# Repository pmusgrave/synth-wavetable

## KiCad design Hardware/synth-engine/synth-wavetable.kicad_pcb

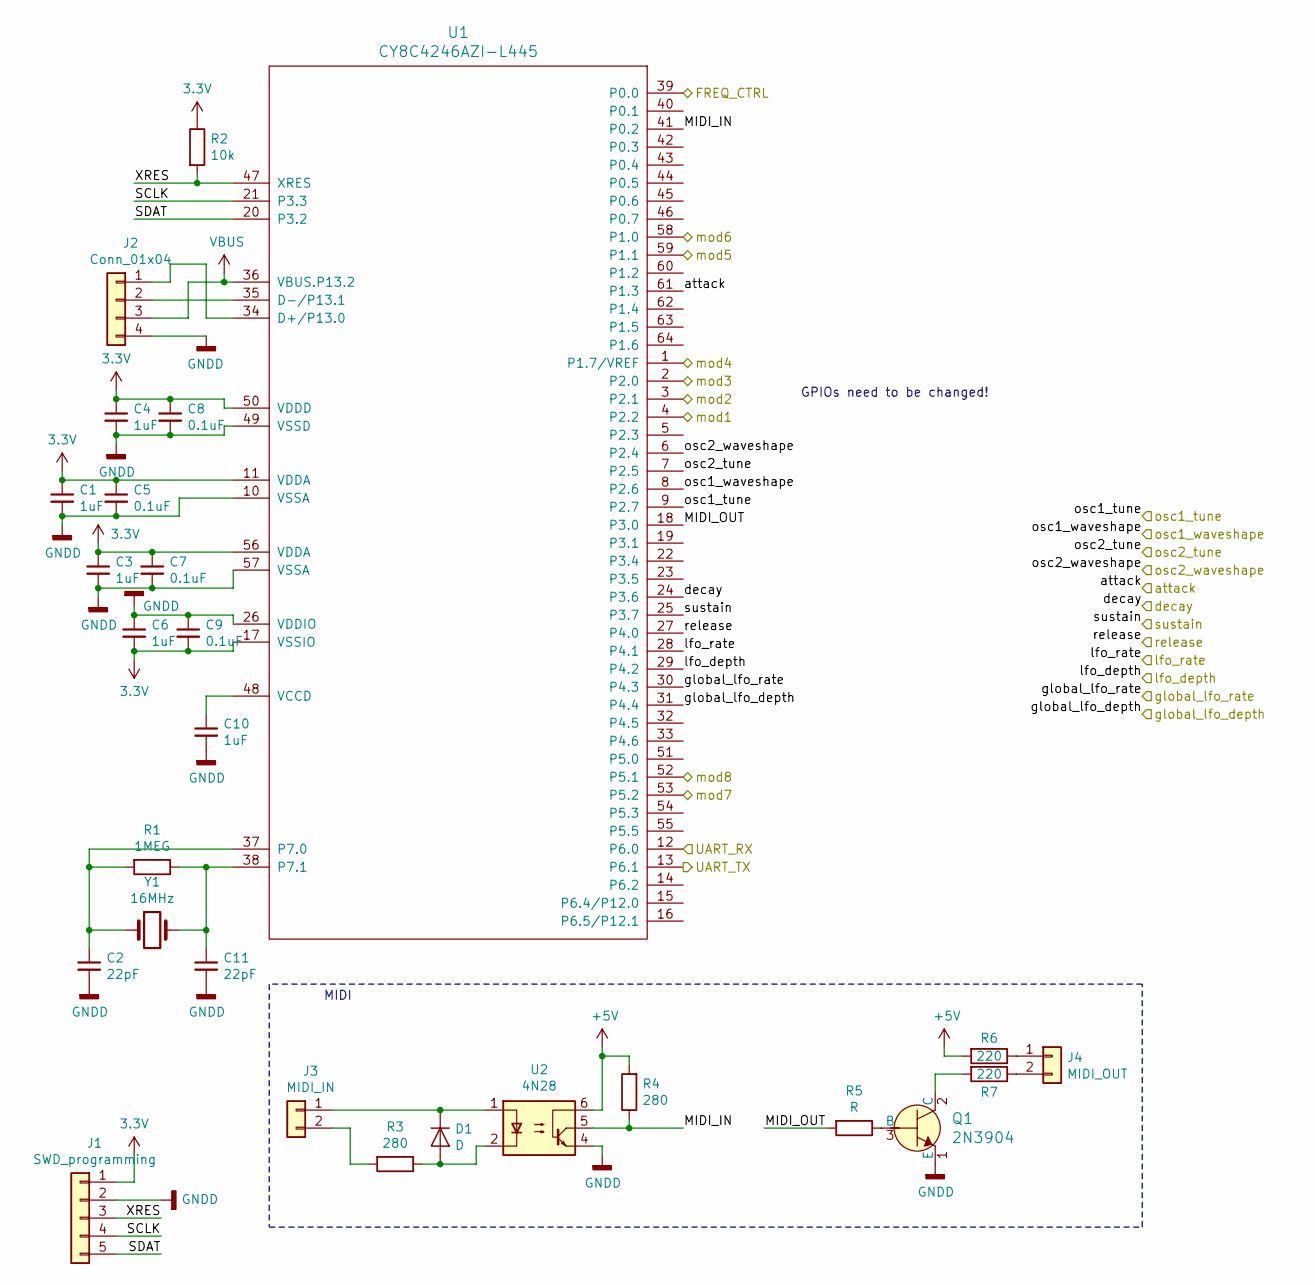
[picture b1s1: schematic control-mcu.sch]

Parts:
C1, C3, C4, C6, C10: 1uF; 0805
C2, C11: 22pF; 0805
C5, C7, C8, C9: 0.1uF; 0805
D1: D; 1210
J1: SWD_programming; 1X05
J2: Conn_01x04; 1X04
J3: MIDI_IN; 1X02
J4: MIDI_OUT; 1X02
Q1: 2N3904; SOT23-3; MPN 2N3904; Digi-Key_PN 2N3904CS-ND
R1: 1MEG; 0805
R2: 10k; 0805
R3, R4: 280; 0805
R5: R; 0805
R6, R7: 220; 0805
U1: CY8C4246AZI-L445; TQFP64
U2: 4N28; DIL-08
Y1: 16MHz; Crystal_SMD_HC49-SD_HandSoldering

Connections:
3.3V: C1.1, C3.1, C4.1, C5.1, C6.2, C7.1, C8.1, C9.2, J1.1, R2.1, U1.11 (VDDA), U1.17 (VSSIO), U1.50 (VDDD), U1.56 (VDDA); also elsewhere on the board
+5V: R4.2, R6.2, U2.6; also elsewhere on the board
/Connectors/attack: U1.61 (P1.3); also elsewhere on the board
/Connectors/decay: U1.24 (P3.6); also elsewhere on the board
/Connectors/global_lfo_depth: U1.31 (P4.4); also elsewhere on the board
/Connectors/global_lfo_rate: U1.30 (P4.3); also elsewhere on the board
/Connectors/lfo_depth: U1.29 (P4.2); also elsewhere on the board
/Connectors/lfo_rate: U1.28 (P4.1); also elsewhere on the board
/Connectors/mod1: U1.4 (P2.2); also elsewhere on the board
/Connectors/mod2: U1.3 (P2.1); also elsewhere on the board
/Connectors/mod3: U1.2 (P2.0); also elsewhere on the board
/Connectors/mod4: U1.1 (P1.7/VREF); also elsewhere on the board
/Connectors/mod5: U1.59 (P1.1); also elsewhere on the board
/Connectors/mod6: U1.58 (P1.0); also elsewhere on the board
/Connectors/mod7: U1.53 (P5.2); also elsewhere on the board
/Connectors/mod8: U1.52 (P5.1); also elsewhere on the board
/Connectors/osc1_tune: U1.9 (P2.7); also elsewhere on the board
/Connectors/osc1_waveshape: U1.8 (P2.6); also elsewhere on the board
/Connectors/osc2_tune: U1.7 (P2.5); also elsewhere on the board
/Connectors/osc2_waveshape: U1.6 (P2.4); also elsewhere on the board
/Connectors/release: U1.27 (P4.0); also elsewhere on the board
/Connectors/sustain: U1.25 (P3.7); also elsewhere on the board
/Control/FREQ_CTRL: U1.39 (P0.0)
/Control/MIDI_IN: R4.1, U1.41 (P0.2), U2.5
/Control/MIDI_OUT: R5.2, U1.18 (P3.0)
/Control/SCLK: J1.4, U1.21 (P3.3)
/Control/SDAT: J1.5, U1.20 (P3.2)
/Control/UART_RX: U1.12 (P6.0)
/Control/UART_TX: U1.13 (P6.1)
/Control/XRES: J1.3, R2.2, U1.47 (XRES)
GNDD: C1.2, C2.2, C3.2, C4.2, C5.2, C6.1, C7.2, C8.2, C9.1, C10.2, C11.2, J1.2, J2.4, Q1.1 (E), U1.10 (VSSA), U1.26 (VDDIO), U1.49 (VSSD), U1.57 (VSSA), U2.4; also elsewhere on the board
unnamed: C2.1, R1.2, U1.37 (P7.0), Y1.1
unnamed: C10.1, U1.48 (VCCD)
unnamed: C11.1, R1.1, U1.38 (P7.1), Y1.2
unnamed: D1.1 (K), J3.1, U2.1
unnamed: D1.2 (A), R3.1, U2.2
unnamed: J2.1, U1.34 (D+/P13.0)
unnamed: J2.2, U1.35 (D-/P13.1)
unnamed: J3.2, R3.2
unnamed: J4.1, R6.1
unnamed: J4.2, R7.1
unnamed: Q1.2 (C), R7.2
unnamed: Q1.3 (B), R5.1
VBUS: J2.3, U1.36 (VBUS.P13.2)

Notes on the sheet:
MIDI
GPIOs need to be changed!

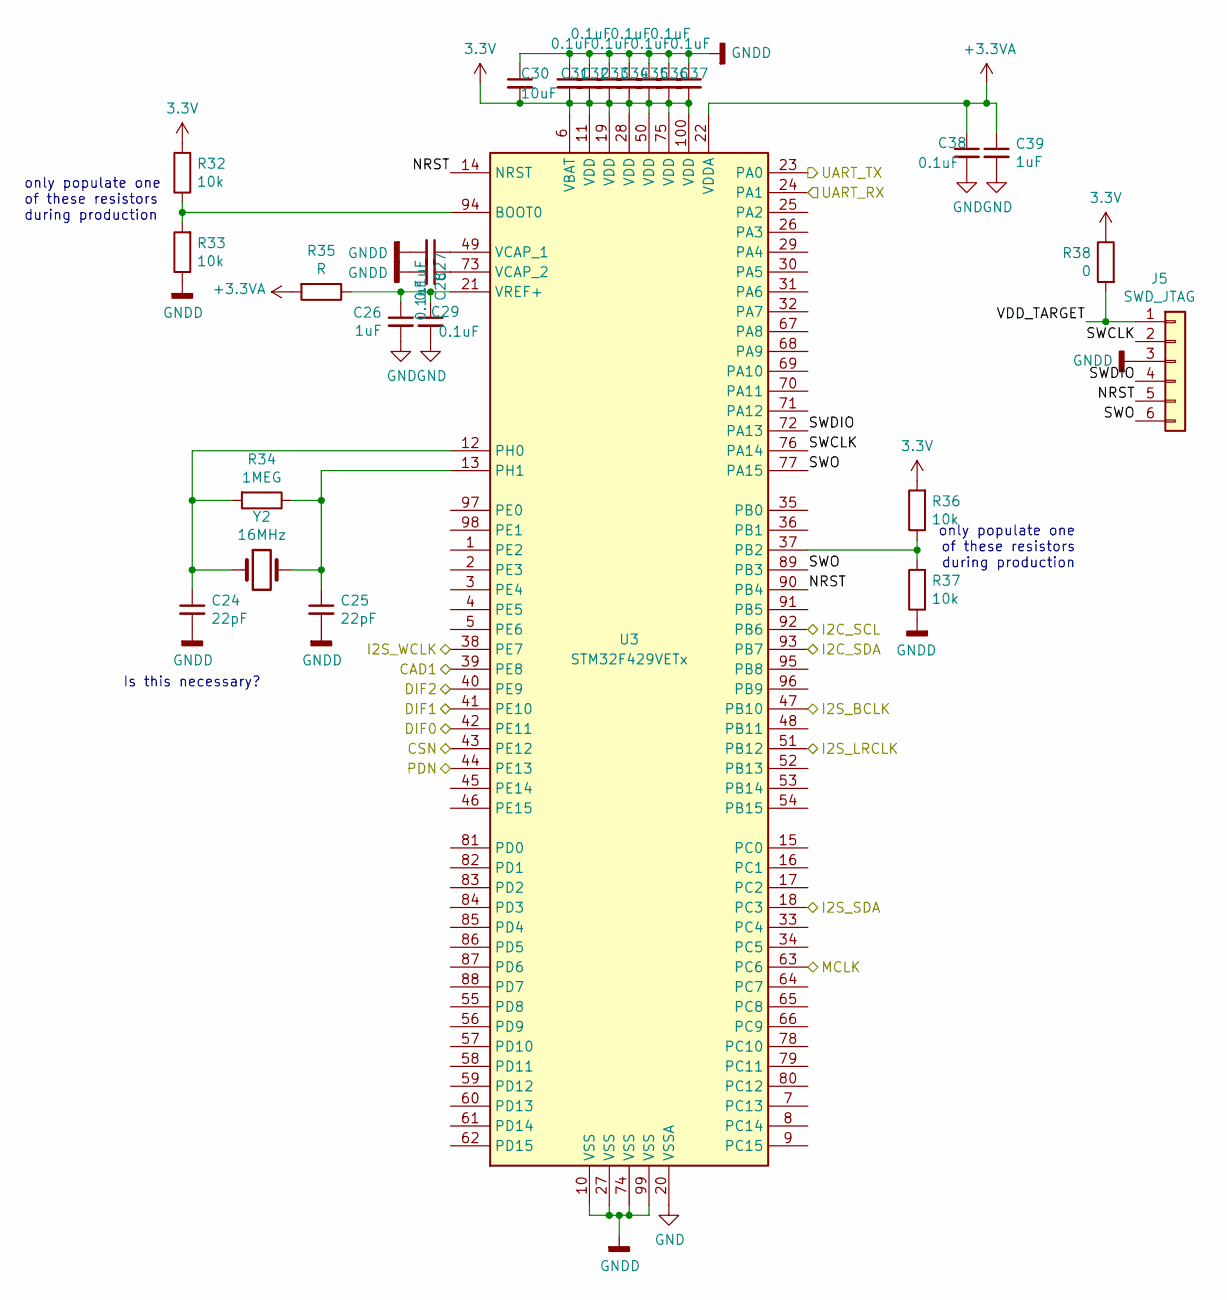
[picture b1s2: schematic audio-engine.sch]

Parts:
C24, C25: 22pF; 0805
C26, C39: 1uF; 0805
C27, C28, C29, C31, C32, C33, C34, C35, C36, C37, C38: 0.1uF; 0805
C30: 10uF; 0805
J5: SWD_JTAG; 1X06
R32, R33, R36, R37: 10k; 0805
R34: 1MEG; 0805
R35: R; 0805
R38: 0; 0805
U3: STM32F429VETx; LQFP-100_14x14mm_P0.5mm
Y2: 16MHz; Crystal_SMD_HC49-SD_HandSoldering

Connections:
3.3V: C30.2, C31.2, C32.2, C33.2, C34.2, C35.2, C36.2, C37.2, R32.2, R36.2, R38.1, U3.6 (VBAT), U3.11 (VDD), U3.19 (VDD), U3.28 (VDD), U3.50 (VDD), U3.75 (VDD), U3.100 (VDD); also elsewhere on the board
+3.3VA: C38.1, C39.1, R35.2, U3.22 (VDDA); also elsewhere on the board
/Audio Engine/CAD1: U3.39 (PE8); also elsewhere on the board
/Audio Engine/CSN: U3.43 (PE12); also elsewhere on the board
/Audio Engine/DIF0: U3.42 (PE11); also elsewhere on the board
/Audio Engine/DIF1: U3.41 (PE10); also elsewhere on the board
/Audio Engine/DIF2: U3.40 (PE9); also elsewhere on the board
/Audio Engine/I2C_SCL: U3.92 (PB6); also elsewhere on the board
/Audio Engine/I2C_SDA: U3.93 (PB7); also elsewhere on the board
/Audio Engine/I2S_BCLK: U3.47 (PB10); also elsewhere on the board
/Audio Engine/I2S_LRCLK: U3.51 (PB12); also elsewhere on the board
/Audio Engine/I2S_SDA: U3.18 (PC3); also elsewhere on the board
/Audio Engine/I2S_WCLK: U3.38 (PE7); also elsewhere on the board
/Audio Engine/MCLK: U3.63 (PC6); also elsewhere on the board
/Audio Engine/NRST: J5.5, U3.14 (NRST), U3.90 (PB4)
/Audio Engine/PDN: U3.44 (PE13); also elsewhere on the board
/Audio Engine/SWCLK: J5.2, U3.76 (PA14)
/Audio Engine/SWDIO: J5.4, U3.72 (PA13)
/Audio Engine/SWO: J5.6, U3.77 (PA15), U3.89 (PB3)
/Audio Engine/UART_RX: U3.24 (PA1)
/Audio Engine/UART_TX: U3.23 (PA0)
/Audio Engine/VDD_TARGET: J5.1, R38.2
GNDD: C24.2, C25.2, C27.2, C28.2, C30.1, C31.1, C32.1, C33.1, C34.1, C35.1, C36.1, C37.1, J5.3, R33.1, R37.1, U3.10 (VSS), U3.27 (VSS), U3.74 (VSS), U3.99 (VSS); also elsewhere on the board
unnamed: C24.1, R34.2, U3.12 (PH0), Y2.1
unnamed: C25.1, R34.1, U3.13 (PH1), Y2.2
unnamed: C26.1, C29.1, R35.1, U3.21 (VREF+)
unnamed: C27.1, U3.49 (VCAP_1)
unnamed: C28.1, U3.73 (VCAP_2)
unnamed: R32.1, R33.2, U3.94 (BOOT0)
unnamed: R36.1, R37.2, U3.37 (PB2)

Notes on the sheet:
only populate one of these resistors during production
Is this necessary?

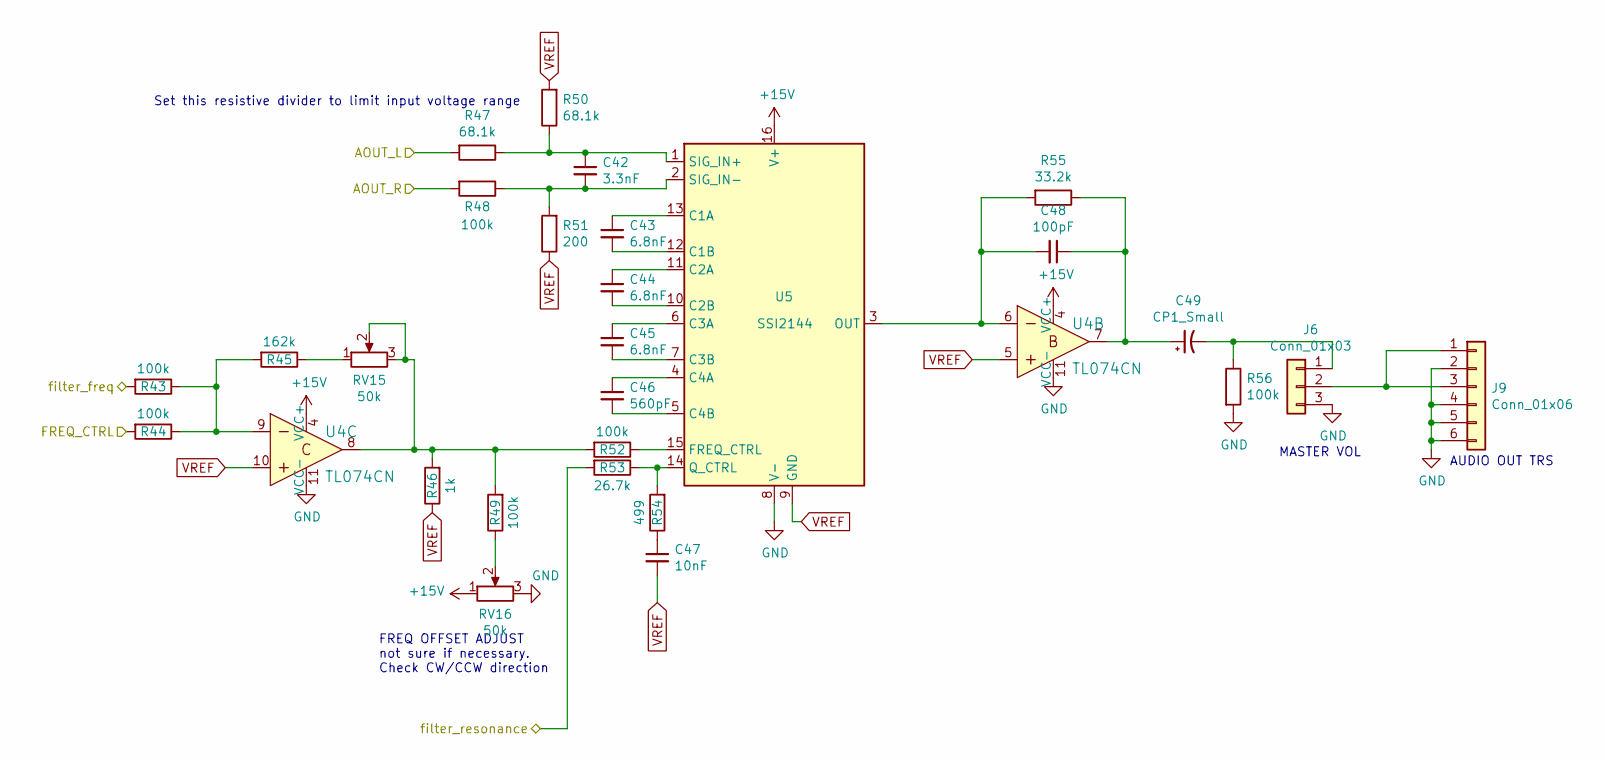
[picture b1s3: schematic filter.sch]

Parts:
C42: 3.3nF; 0805
C43, C44, C45: 6.8nF; 0805
C46: 560pF; 0805
C47: 10nF; 0805
C48: 100pF; 0805
C49: CP1_Small; CP_Elec_6.3x5.4
J6: Conn_01x03; 1X03
J9: Conn_01x06; 1X06
R43, R44, R48, R49, R52, R56: 100k; 0805
R45: 162k; 0805
R46: 1k; 0805
R47, R50: 68.1k; 0805
R51: 200; 0805
R53: 26.7k; 0805
R54: 499; 0805
R55: 33.2k; 0805
RV15, RV16: 50k; TRIMPOT-3MM-2
U4: TL074CN; SO16; MPN TL074CN; Digi-Key_PN 296-1777-5-ND
U5: SSI2144; SSOP16

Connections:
/Connectors/filter_freq: R43.2; also elsewhere on the board
/Connectors/filter_resonance: R53.2; also elsewhere on the board
/DAC/AOUT_L: R47.2; also elsewhere on the board
/DAC/AOUT_R: R48.2; also elsewhere on the board
/Filter/FREQ_CTRL: R44.2
unnamed: C42.1, R47.1, R50.1, U5.1 (SIG_IN+)
unnamed: C42.2, R48.1, R51.2, U5.2 (SIG_IN-)
unnamed: C43.1, U5.13 (C1A)
unnamed: C43.2, U5.12 (C1B)
unnamed: C44.1, U5.11 (C2A)
unnamed: C44.2, U5.10 (C2B)
unnamed: C45.1, U5.6 (C3A)
unnamed: C45.2, U5.7 (C3B)
unnamed: C46.1, U5.4 (C4A)
unnamed: C46.2, U5.5 (C4B)
unnamed: C47.1, R54.1
unnamed: C48.1, C49.1, R55.1, U4.7
unnamed: C48.2, R55.2, U4.6, U5.3 (OUT)
unnamed: C49.2, J6.1, R56.1
unnamed: J6.2, J9.1, J9.3
unnamed: R43.1, R44.1, R45.2, U4.9
unnamed: R45.1, RV15.1
unnamed: R46.2, R49.2, R52.2, RV15.2, RV15.3, U4.8
unnamed: R49.1, RV16.2
unnamed: R52.1, U5.15 (FREQ_CTRL)
unnamed: R53.1, R54.2, U5.14 (Q_CTRL)
VREF: C47.2, R46.1, R50.2, R51.1, U4.5, U4.10, U5.9 (GND); also elsewhere on the board

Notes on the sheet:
FREQ OFFSET ADJUST not sure if necessary. Check CW/CCW direction
Set this resistive divider to limit input voltage range
MASTER VOL
AUDIO OUT TRS

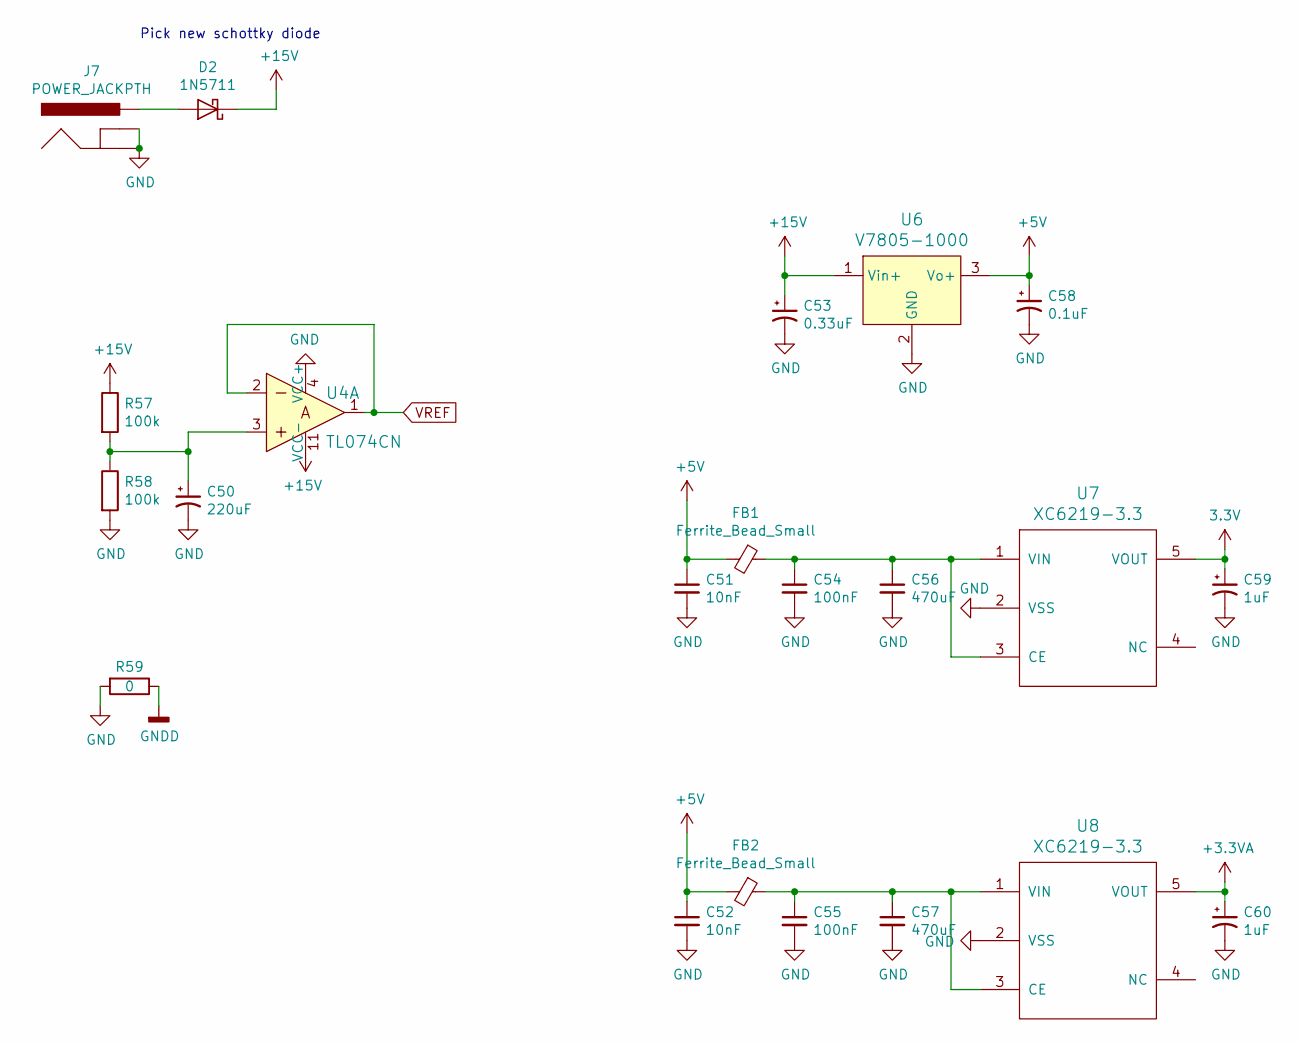
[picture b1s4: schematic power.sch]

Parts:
C50: 220uF; CP_Elec_6.3x5.4
C51, C52: 10nF; 0805
C53: 0.33uF; 0805
C54, C55: 100nF; 0805
C56, C57: 470uF; CP_Elec_6.3x5.4
C58: 0.1uF; 0805
C59, C60: 1uF; 0805
D2: 1N5711; 1210
FB1, FB2: Ferrite_Bead_Small; 0805
J7: POWER_JACKPTH; POWER_JACK_PTH
R57, R58: 100k; 0805
R59: 0; 0805
U4: TL074CN; SO16; MPN TL074CN; Digi-Key_PN 296-1777-5-ND
U6: V7805-1000; TO220V; MPN V7805-1000; Digi-Key_PN 102-1715-ND
U7, U8: XC6219-3.3; SOT23-5

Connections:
3.3V: C59.1, U7.5 (VOUT); also elsewhere on the board
+3.3VA: C60.1, U8.5 (VOUT); also elsewhere on the board
+5V: C51.1, C52.1, C58.1, FB1.2, FB2.2, U6.3 (Vo+); also elsewhere on the board
GNDD: R59.1; also elsewhere on the board
unnamed: C50.1, R57.2, R58.1, U4.3
unnamed: C54.1, C56.1, FB1.1, U7.1 (VIN), U7.3 (CE)
unnamed: C55.1, C57.1, FB2.1, U8.1 (VIN), U8.3 (CE)
unnamed: D2.2 (A), J7.PWR
VREF: U4.1, U4.2; also elsewhere on the board

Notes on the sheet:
Pick new schottky diode

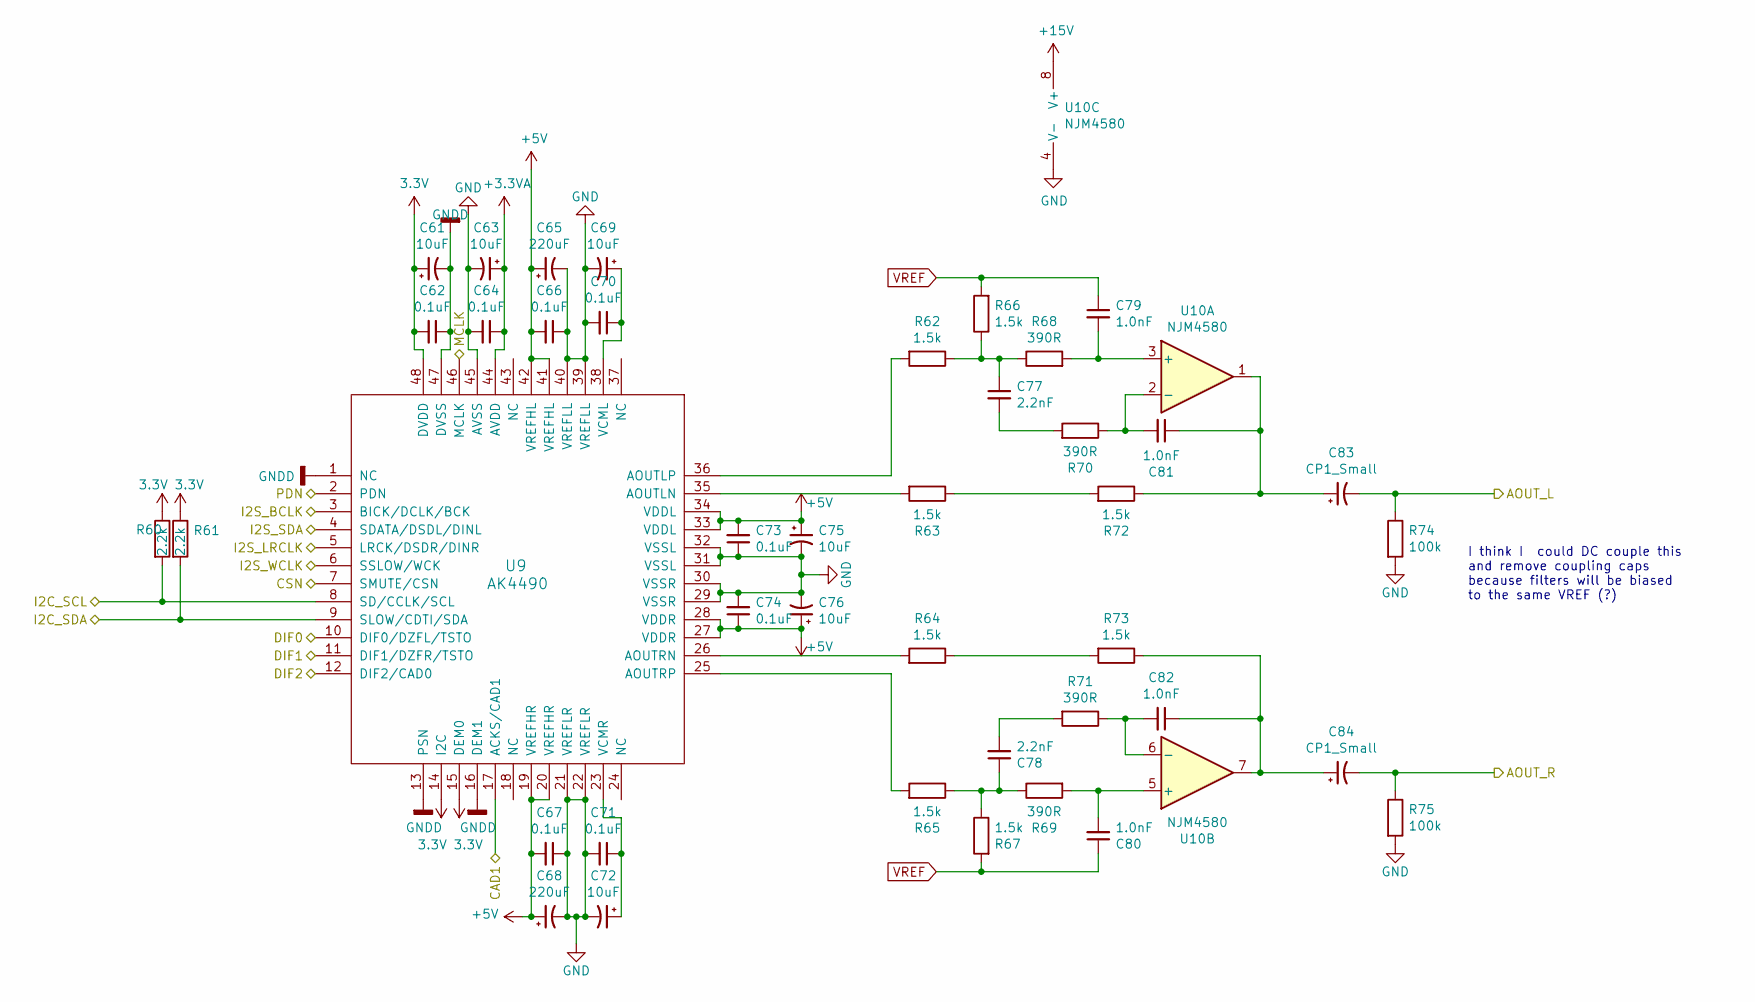
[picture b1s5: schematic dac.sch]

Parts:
C61, C63, C69, C72, C75, C76: 10uF; CP_Elec_6.3x5.4
C62, C64, C66, C67, C70, C71, C73, C74: 0.1uF; 0805
C65, C68: 220uF; CP_Elec_6.3x5.4
C77, C78: 2.2nF; 0805
C79, C80, C81, C82: 1.0nF; 0805
C83, C84: CP1_Small; CP_Elec_6.3x5.4
R60, R61: 2.2k; 0805
R62, R63, R64, R65, R66, R67, R72, R73: 1.5k; 0805
R68, R69, R70, R71: 390R; 0805
R74, R75: 100k; 0805
U9: AK4490; LQFP-48
U10: NJM4580; SO08

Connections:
3.3V: C61.1, C62.2, R60.1, R61.1, U9.14 (I2C), U9.15 (DEM0), U9.48 (DVDD); also elsewhere on the board
+3.3VA: C63.1, C64.1, U9.44 (AVDD); also elsewhere on the board
+5V: C65.1, C66.2, C67.2, C68.1, C73.2, C74.1, C75.1, C76.1, U9.19 (VREFHR), U9.20 (VREFHR), U9.27 (VDDR), U9.28 (VDDR), U9.33 (VDDL), U9.34 (VDDL), U9.41 (VREFHL), U9.42 (VREFHL); also elsewhere on the board
/Audio Engine/CAD1: U9.17 (ACKS/CAD1); also elsewhere on the board
/Audio Engine/CSN: U9.7 (SMUTE/CSN); also elsewhere on the board
/Audio Engine/DIF0: U9.10 (DIF0/DZFL/TSTO); also elsewhere on the board
/Audio Engine/DIF1: U9.11 (DIF1/DZFR/TSTO); also elsewhere on the board
/Audio Engine/DIF2: U9.12 (DIF2/CAD0); also elsewhere on the board
/Audio Engine/I2C_SCL: R60.2, U9.8 (SD/CCLK/SCL); also elsewhere on the board
/Audio Engine/I2C_SDA: R61.2, U9.9 (SLOW/CDTI/SDA); also elsewhere on the board
/Audio Engine/I2S_BCLK: U9.3 (BICK/DCLK/BCK); also elsewhere on the board
/Audio Engine/I2S_LRCLK: U9.5 (LRCK/DSDR/DINR); also elsewhere on the board
/Audio Engine/I2S_SDA: U9.4 (SDATA/DSDL/DINL); also elsewhere on the board
/Audio Engine/I2S_WCLK: U9.6 (SSLOW/WCK); also elsewhere on the board
/Audio Engine/MCLK: U9.46 (MCLK); also elsewhere on the board
/Audio Engine/PDN: U9.2 (PDN); also elsewhere on the board
/DAC/AOUT_L: C83.2, R74.1; also elsewhere on the board
/DAC/AOUT_R: C84.2, R75.1; also elsewhere on the board
GNDD: C61.2, C62.1, U9.1 (NC), U9.13 (PSN), U9.16 (DEM1), U9.47 (DVSS); also elsewhere on the board
unnamed: C69.1, C70.1, U9.38 (VCML)
unnamed: C71.1, C72.1, U9.23 (VCMR)
unnamed: C77.1, R62.1, R66.1, R68.1
unnamed: C77.2, R70.2
unnamed: C78.1, R65.1, R67.1, R69.1
unnamed: C78.2, R71.2
unnamed: C79.2, R68.2, U10.3 (+)
unnamed: C80.2, R69.2, U10.5 (+)
unnamed: C81.1, C83.1, R72.1, U10.1
unnamed: C81.2, R70.1, U10.2 (-)
unnamed: C82.1, C84.1, R73.1, U10.7
unnamed: C82.2, R71.1, U10.6 (-)
unnamed: R62.2, U9.36 (AOUTLP)
unnamed: R63.1, R72.2
unnamed: R63.2, U9.35 (AOUTLN)
unnamed: R64.1, R73.2
unnamed: R64.2, U9.26 (AOUTRN)
unnamed: R65.2, U9.25 (AOUTRP)
VREF: C79.1, C80.1, R66.2, R67.2; also elsewhere on the board

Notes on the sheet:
I think I could DC couple this and remove coupling caps because filters will be biased to the same VREF (?)

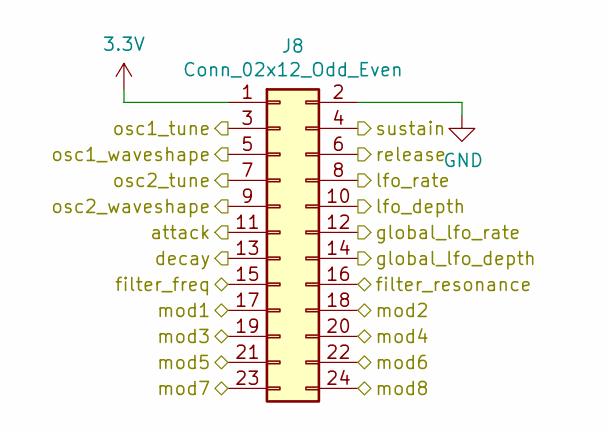
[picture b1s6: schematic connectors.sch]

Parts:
J8: Conn_02x12_Odd_Even; 2X12

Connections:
3.3V: J8.1; also elsewhere on the board
/Connectors/attack: J8.11; also elsewhere on the board
/Connectors/decay: J8.13; also elsewhere on the board
/Connectors/filter_freq: J8.15; also elsewhere on the board
/Connectors/filter_resonance: J8.16; also elsewhere on the board
/Connectors/global_lfo_depth: J8.14; also elsewhere on the board
/Connectors/global_lfo_rate: J8.12; also elsewhere on the board
/Connectors/lfo_depth: J8.10; also elsewhere on the board
/Connectors/lfo_rate: J8.8; also elsewhere on the board
/Connectors/mod1: J8.17; also elsewhere on the board
/Connectors/mod2: J8.18; also elsewhere on the board
/Connectors/mod3: J8.19; also elsewhere on the board
/Connectors/mod4: J8.20; also elsewhere on the board
/Connectors/mod5: J8.21; also elsewhere on the board
/Connectors/mod6: J8.22; also elsewhere on the board
/Connectors/mod7: J8.23; also elsewhere on the board
/Connectors/mod8: J8.24; also elsewhere on the board
/Connectors/osc1_tune: J8.3; also elsewhere on the board
/Connectors/osc1_waveshape: J8.5; also elsewhere on the board
/Connectors/osc2_tune: J8.7; also elsewhere on the board
/Connectors/osc2_waveshape: J8.9; also elsewhere on the board
/Connectors/release: J8.6; also elsewhere on the board
/Connectors/sustain: J8.4; also elsewhere on the board

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
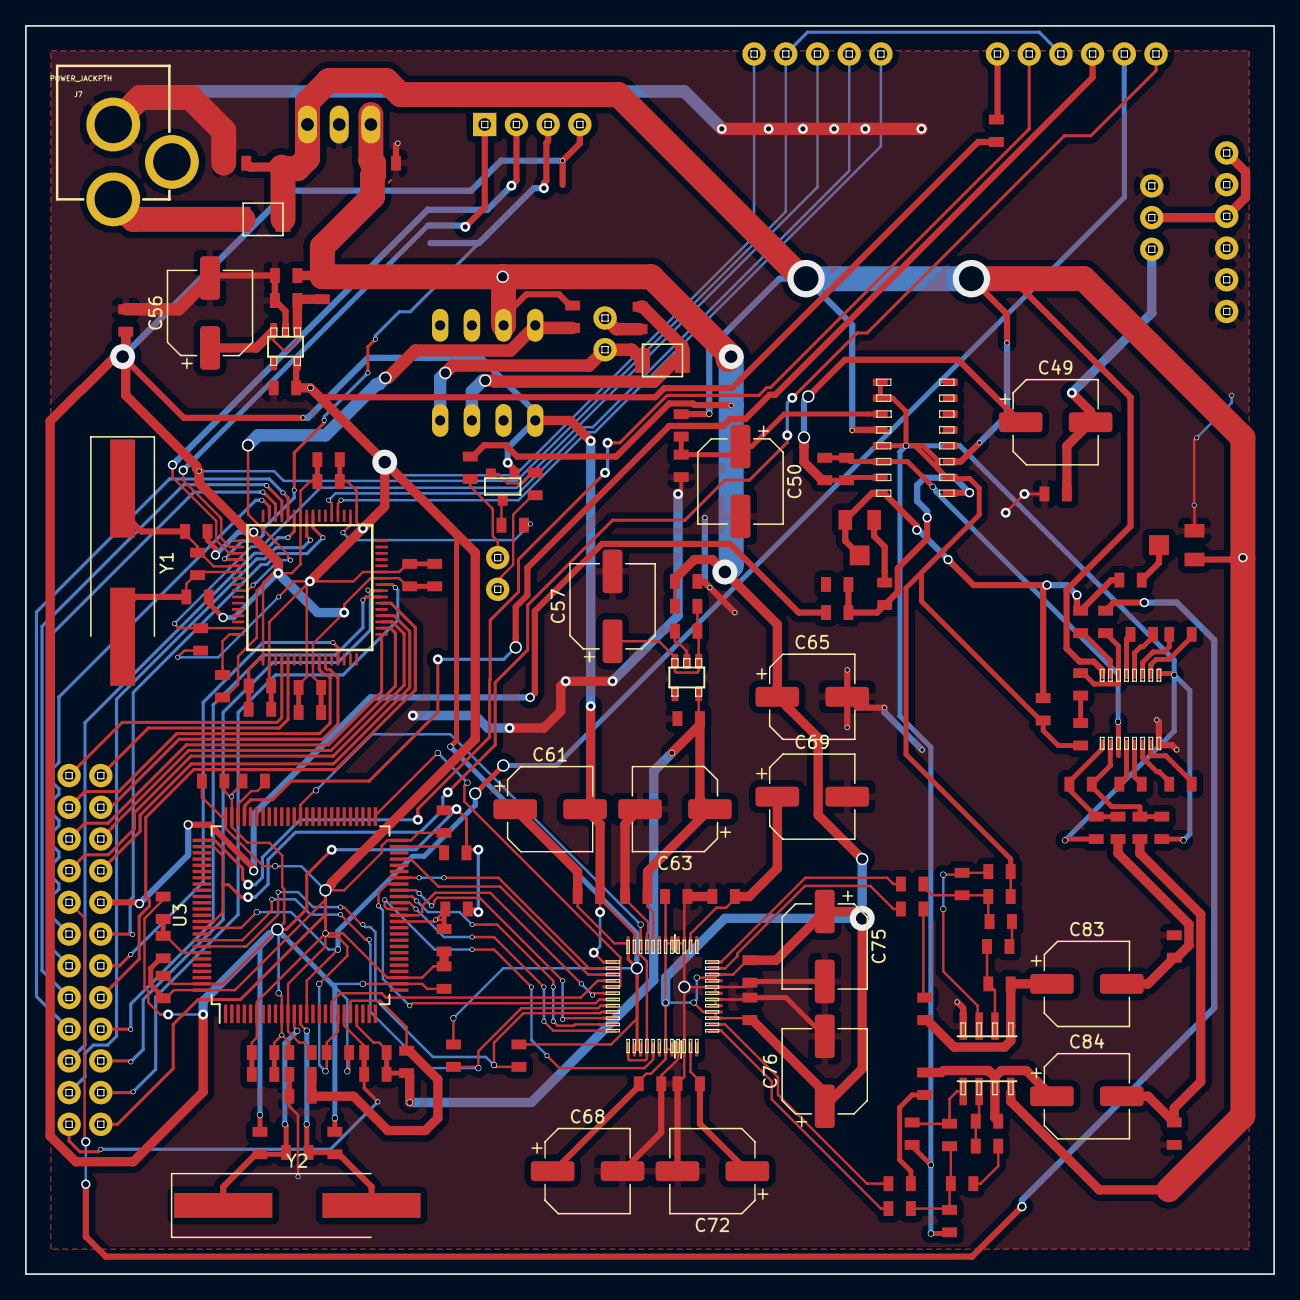
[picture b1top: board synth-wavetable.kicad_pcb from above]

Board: 2 copper layers, 100.0 x 100.0 mm, 145 parts (1 on the bottom side), 117 nets.

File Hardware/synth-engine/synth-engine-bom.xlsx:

In Stock? | Reference | Quantity | Value | Footprint | Datasheet | Category | DK_Datasheet_Link | DK_Detail_Page | Description | Digi-Key_PN | Family | MPN | Manufacturer | Status
Y | C11 C2 C24 C25 | 4 | 22pF | SparkFun-Passives:0805 | ~
Y | C30 | 1 | 10uF | SparkFun-Passives:0805 | ~
On Order | C1 C10 C26 C3 C39 C4 C59 C6 C60 | 9 | 1uF | SparkFun-Passives:0805 | ~
Y | C42 | 1 | 3.3nF | SparkFun-Passives:0805 | ~
On Order | C43 C44 C45 | 3 | 6.8nF | SparkFun-Passives:0805 | ~
On Order | C46 | 1 | 560pF | SparkFun-Passives:0805 | ~
Y | C47 C51 C52 | 3 | 10nF | SparkFun-Passives:0805 | ~
Y | C48 | 1 | 100pF | SparkFun-Passives:0805 | ~
Y | C49 C83 C84 | 3 | CP1_Small | Capacitor_SMD:CP_Elec_6.3x5.4 | ~
Y | C50 C65 C68 | 3 | 220uF | Capacitor_SMD:CP_Elec_6.3x5.4 | ~
Y | C53 | 1 | 0.33uF | SparkFun-Passives:0805 | ~
Y | C54 C55 | 2 | 100nF | SparkFun-Passives:0805 | ~
Y | C56 C57 | 2 | 470uF | Capacitor_SMD:CP_Elec_6.3x5.4 | ~
Y | C61 C63 C69 C72 C75 C76 | 6 | 10uF | Capacitor_SMD:CP_Elec_6.3x5.4 | ~
Y | C77 C78 | 2 | 2.2nF | SparkFun-Passives:0805 | ~
Y | C79 C80 C81 C82 | 4 | 1.0nF | SparkFun-Passives:0805 | ~
Y | C27 C28 C29 C31 C32 C33 C34 C35 C36 C37 C38 C5 C58 C62 C64 C66 C67 C7 C70 C71 C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 | 24 | 0.1uF | SparkFun-Passives:0805 | ~
Y | D1 | 1 | D | SparkFun-Passives:1210 | ~
Y | D2 | 1 | 1N5711 | SparkFun-Passives:1210 | https://www.microsemi.com/document-portal/doc_download/8865-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
Y | FB1 FB2 | 2 | Ferrite_Bead_Small | SparkFun-Passives:0805 | ~
 | J1 | 1 | SWD_programming | SparkFun-Connectors:1X05 | ~
 | J2 | 1 | Conn_01x04 | SparkFun-Connectors:1X04 | ~
 | J3 | 1 | MIDI_IN | SparkFun-Connectors:1X02 | ~
 | J4 | 1 | MIDI_OUT | SparkFun-Connectors:1X02 | ~
 | J5 | 1 | SWD_JTAG | SparkFun-Connectors:1X06 | ~
 | J6 | 1 | Conn_01x03 | SparkFun-Connectors:1X03 | ~
 | J7 | 1 | POWER_JACKPTH | SparkFun-Connectors:POWER_JACK_PTH
 | J8 | 1 | Conn_02x12_Odd_Even | SparkFun-Connectors:2X12 | ~
 | J9 | 1 | Conn_01x06 | SparkFun-Connectors:1X06 | ~
Y | Q1 | 1 | 2N3904 | SparkFun-DiscreteSemi:SOT23-3 | https://my.centralsemi.com/get_document.php?cmp=1&mergetype=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 | Discrete Semiconductor Products | https://my.centralsemi.com/get_document.php?cmp=1&mergetype=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 | /product-detail/en/central-semiconductor-corp/2N3904/2N3904CS-ND/4806876 | TRANS NPN 40V TO-92 | 2N3904CS-ND | Transistors - Bipolar (BJT) - Single | 2N3904 | Central Semiconductor Corp | Active
Y | R1 R34 | 2 | 1MEG | SparkFun-Passives:0805 | ~
Y | R2 R32 R33 R36 R37 | 5 | 10k | SparkFun-Passives:0805 | ~
Y | R3 R4 | 2 | 280 | SparkFun-Passives:0805 | ~
Y | R38 R59 | 2 | 0 | SparkFun-Passives:0805 | ~
On Order | R45 | 1 | 162k | SparkFun-Passives:0805 | ~
Y | R46 | 1 | 1k | SparkFun-Passives:0805 | ~
On Order | R47 R50 | 2 | 68.1k | SparkFun-Passives:0805 | ~
Y | R43 R44 R48 R49 R52 R56 R57 R58 R74 R75 | 10 | 100k | SparkFun-Passives:0805 | ~
Y | R35 R5 | 2 | R | SparkFun-Passives:0805 | ~
Y | R51 | 1 | 200 | SparkFun-Passives:0805 | ~
On Order | R53 | 1 | 26.7k | SparkFun-Passives:0805 | ~
Y | R54 | 1 | 499 | SparkFun-Passives:0805 | ~
Y | R55 | 1 | 33.2k | SparkFun-Passives:0805 | ~
Y | R6 R7 | 2 | 220 | SparkFun-Passives:0805 | ~
Y | R60 R61 | 2 | 2.2k | SparkFun-Passives:0805 | ~
Y | R62 R63 R64 R65 R66 R67 R72 R73 | 8 | 1.5k | SparkFun-Passives:0805 | ~
On Order | R68 R69 R70 R71 | 4 | 390R | SparkFun-Passives:0805 | ~
Y | RV15 RV16 | 2 | 50k | SparkFun-Electromechanical:TRIMPOT-3MM-2 | ~
Y | U1 | 1 | CY8C4246AZI-L445 | SparkFun-DigitalIC:TQFP64
On Order | U10 | 1 | NJM4580 | SparkFun-DigitalIC:SO08 | http://www.njr.com/semicon/PDF/NJM4580_E.pdf
Y | U2 | 1 | 4N28 | SparkFun-AnalogIC:DIL-08 | https://www.vishay.com/docs/83725/4n25.pdf
On Order | U3 | 1 | STM32F429VETx | Package_QFP:LQFP-100_14x14mm_P0.5mm | http://www.st.com/st-web-ui/static/active/en/resource/techni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
On Order | U4 | 1 | TL074CN | SparkFun-AnalogIC:SO16 | http://www.ti.com/lit/ds/symlink/tl071a.pdf | Integrated Circuits (ICs) | http://www.ti.com/lit/ds/symlink/tl071a.pdf | /product-detail/en/texas-instruments/TL074CN/296-1777-5-ND/277423 | IC OPAMP JFET 3MHZ 14DIP | 296-1777-5-ND | Linear - Amplifiers - Instrumentation, OP Amps, Buffer Amps | TL074CN | Texas Instruments | Active
Y | U5 | 1 | SSI2144 | SparkFun-AnalogIC:SSOP16 | http://www.soundsemiconductor.com/downloads/ssi2144datasheet.pdf
On Order | U6 | 1 | V7805-1000 | SparkFun-DiscreteSemi:TO220V | https://www.cui.com/product/resource/digikeypdf/v78xx-1000.pdf | Power Supplies - Board Mount | https://www.cui.com/product/resource/digikeypdf/v78xx-1000.pdf | /product-detail/en/cui-inc/V7805-1000/102-1715-ND/1828608 | DC DC CONVERTER 5V 5W | 102-1715-ND | DC DC Converters | V7805-1000 | CUI Inc. | Active
Y | U7 U8 | 2 | XC6219-3.3 | SparkFun-DigitalIC:SOT23-5
On Order | U9 | 1 | AK4490 | SparkFun-DigitalIC:LQFP-48
Y | Y1 Y2 | 2 | 16MHz | Crystal:Crystal_SMD_HC49-SD_HandSoldering | ~

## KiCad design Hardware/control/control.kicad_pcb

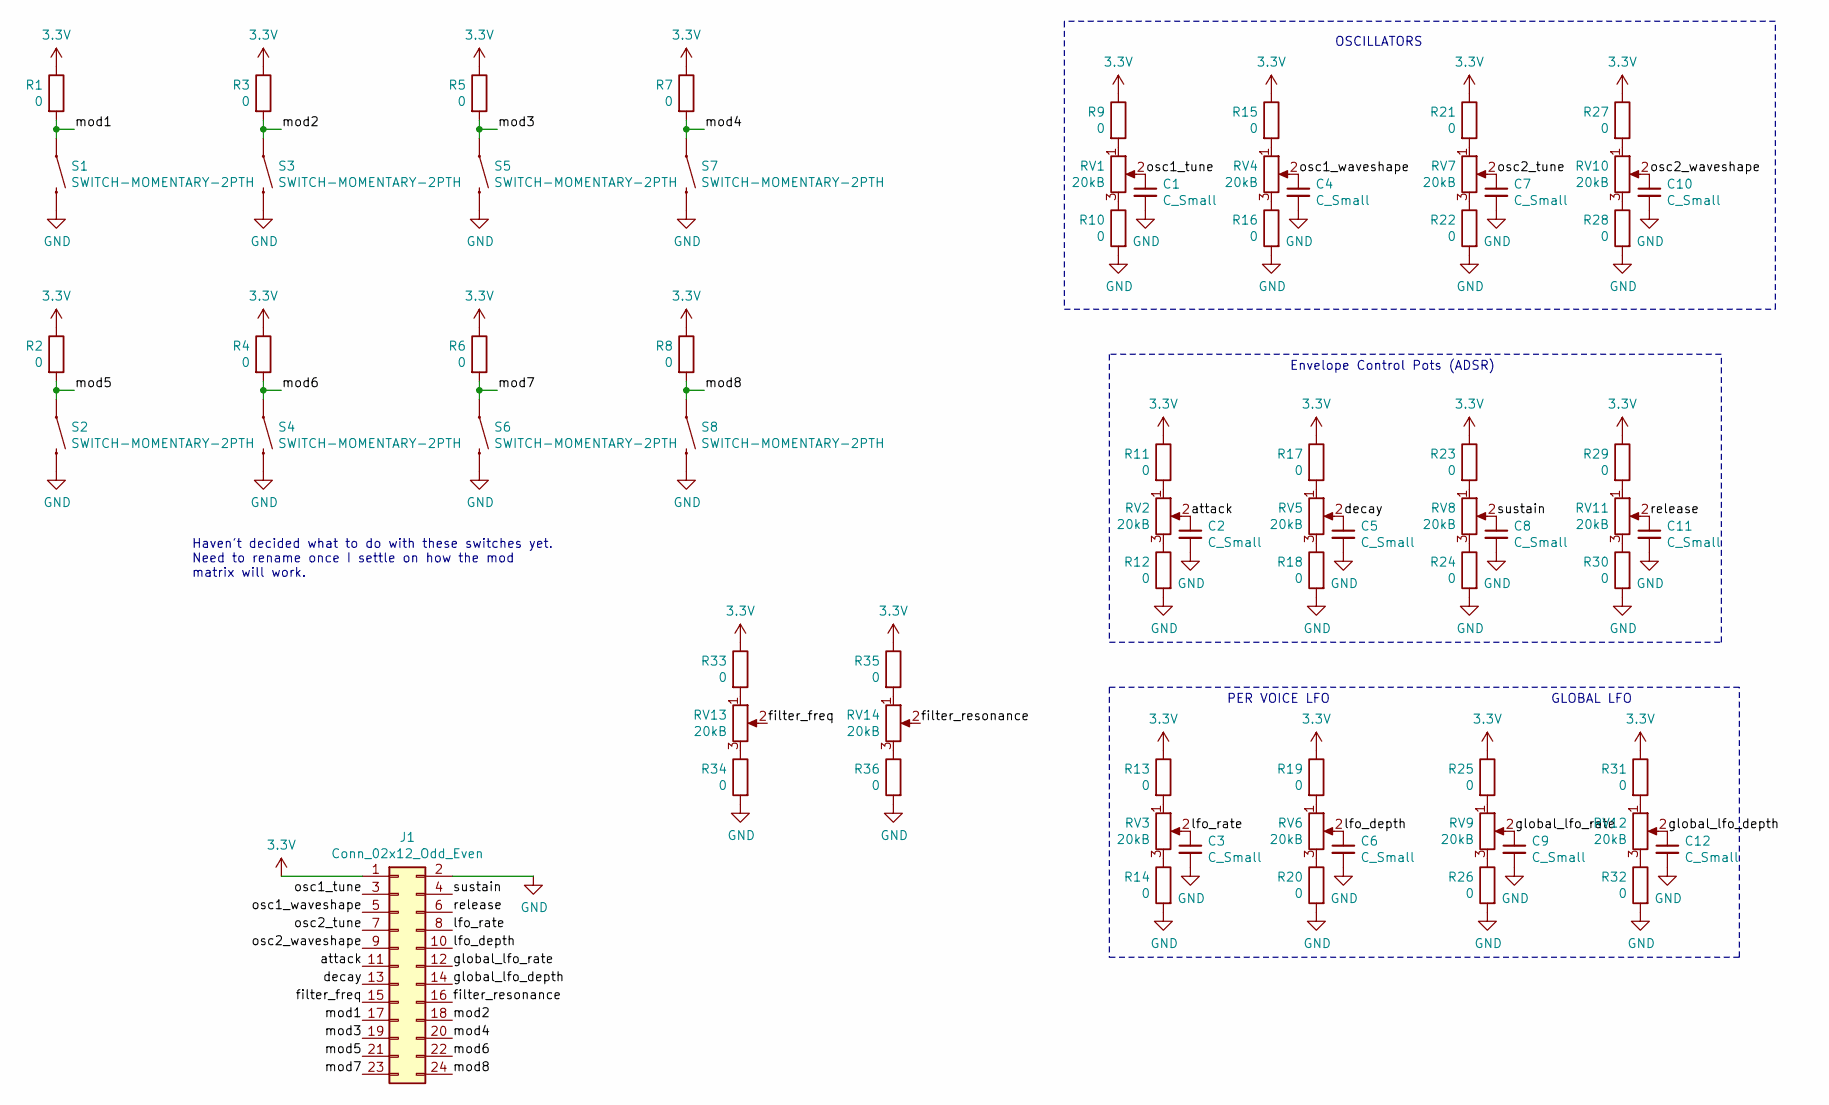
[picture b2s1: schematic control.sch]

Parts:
C1, C2, C3, C4, C5, C6, C7, C8, C9, C10, C11, C12: C_Small; 0805
J1: Conn_02x12_Odd_Even; 2X12
R1, R2, R3, R4, R5, R6, R7, R8, R9, R10, R11, R12, R13, R14, R15, R16, R17, R18, R19, R20, R21, R22, R23, R24, R25, R26, R27, R28, R29, R30, R31, R32, R33, R34, R35, R36: 0; 0805
RV1, RV2, RV3, RV4, RV5, RV6, RV7, RV8, RV9, RV10, RV11, RV12, RV13, RV14: 20kB; Potentiometer_Alps_RK09K_Single_Vertical
S1, S2, S3, S4, S5, S6, S7, S8: SWITCH-MOMENTARY-2PTH; TACTILE-PTH

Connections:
3.3V: J1.1, R1.1, R2.1, R3.1, R4.1, R5.1, R6.1, R7.1, R8.1, R9.1, R11.1, R13.1, R15.1, R17.1, R19.1, R21.1, R23.1, R25.1, R27.1, R29.1, R31.1, R33.1, R35.1
/attack: C2.1, J1.11, RV2.2
/decay: C5.1, J1.13, RV5.2
/filter_freq: J1.15, RV13.2
/filter_resonance: J1.16, RV14.2
/global_lfo_depth: C12.1, J1.14, RV12.2
/global_lfo_rate: C9.1, J1.12, RV9.2
/lfo_depth: C6.1, J1.10, RV6.2
/lfo_rate: C3.1, J1.8, RV3.2
/mod1: J1.17, R1.2, S1.1
/mod2: J1.18, R3.2, S3.1
/mod3: J1.19, R5.2, S5.1
/mod4: J1.20, R7.2, S7.1
/mod5: J1.21, R2.2, S2.1
/mod6: J1.22, R4.2, S4.1
/mod7: J1.23, R6.2, S6.1
/mod8: J1.24, R8.2, S8.1
/osc1_tune: C1.1, J1.3, RV1.2
/osc1_waveshape: C4.1, J1.5, RV4.2
/osc2_tune: C7.1, J1.7, RV7.2
/osc2_waveshape: C10.1, J1.9, RV10.2
/release: C11.1, J1.6, RV11.2
/sustain: C8.1, J1.4, RV8.2
GND: C1.2, C2.2, C3.2, C4.2, C5.2, C6.2, C7.2, C8.2, C9.2, C10.2, C11.2, C12.2, J1.2, R10.2, R12.2, R14.2, R16.2, R18.2, R20.2, R22.2, R24.2, R26.2, R28.2, R30.2, R32.2, R34.2, R36.2, S1.3 (2), S2.3 (2), S3.3 (2), S4.3 (2), S5.3 (2), S6.3 (2), S7.3 (2), S8.3 (2)
unnamed: R9.2, RV1.1
unnamed: R10.1, RV1.3
unnamed: R11.2, RV2.1
unnamed: R12.1, RV2.3
unnamed: R13.2, RV3.1
unnamed: R14.1, RV3.3
unnamed: R15.2, RV4.1
unnamed: R16.1, RV4.3
unnamed: R17.2, RV5.1
unnamed: R18.1, RV5.3
unnamed: R19.2, RV6.1
unnamed: R20.1, RV6.3
unnamed: R21.2, RV7.1
unnamed: R22.1, RV7.3
unnamed: R23.2, RV8.1
unnamed: R24.1, RV8.3
unnamed: R25.2, RV9.1
unnamed: R26.1, RV9.3
unnamed: R27.2, RV10.1
unnamed: R28.1, RV10.3
unnamed: R29.2, RV11.1
unnamed: R30.1, RV11.3
unnamed: R31.2, RV12.1
unnamed: R32.1, RV12.3
unnamed: R33.2, RV13.1
unnamed: R34.1, RV13.3
unnamed: R35.2, RV14.1
unnamed: R36.1, RV14.3

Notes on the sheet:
Envelope Control Pots (ADSR)
GLOBAL LFO
OSCILLATORS
PER VOICE LFO
Haven't decided what to do with these switches yet. Need to rename once I settle on how the mod matrix will work.
